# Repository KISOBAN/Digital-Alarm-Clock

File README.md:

This is a digital clock that has the option of being a stopwatch as well. This was done with the Raspberry PI Pico W using the C SDK and built using CMake.

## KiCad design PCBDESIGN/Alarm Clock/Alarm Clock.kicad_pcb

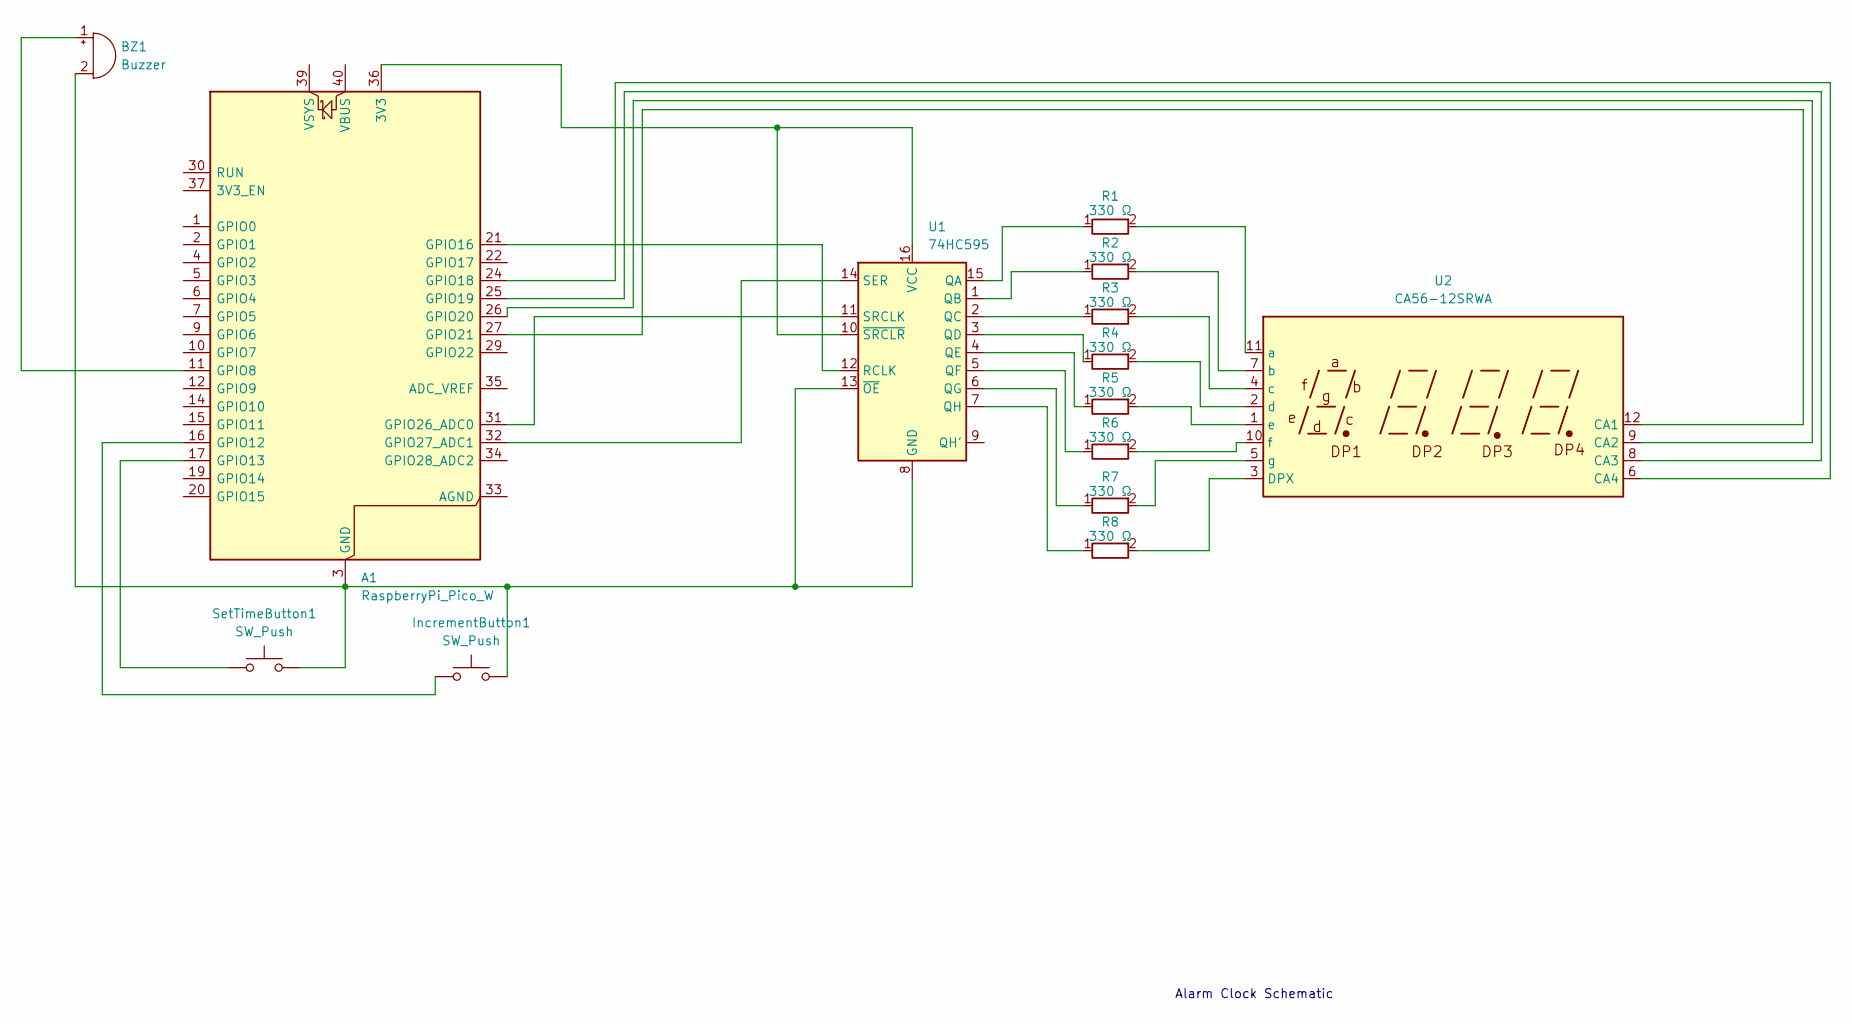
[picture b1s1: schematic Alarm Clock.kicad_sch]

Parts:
A1: RaspberryPi_Pico_W; RaspberryPi_Pico_W_SMD_HandSolder
BZ1: Buzzer; Buzzer_12x9.5RM7.6
IncrementButton1: SW_Push; SW_TH_Tactile_Omron_B3F-106x
R1, R2, R3, R4, R5, R6, R7, R8: 330 Ω; R_Axial_DIN0411_L9.9mm_D3.6mm_P12.70mm_Horizontal
SetTimeButton1: SW_Push; SW_TH_Tactile_Omron_B3F-106x
U1: 74HC595; SN74HCN595N
U2: CA56-12SRWA; 3461AS1 4 digit seven segment display

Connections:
unnamed: A1.36 (3V3), U1.10 (~SRCLR), U1.16 (VCC)
unnamed: A1.11 (GPIO8), BZ1.1 (+)
unnamed: A1.16 (GPIO12), IncrementButton1.1
unnamed: A1.17 (GPIO13), SetTimeButton1.1
unnamed: A1.21 (GPIO16), U1.12 (RCLK)
unnamed: A1.24 (GPIO18), U2.6 (CA4)
unnamed: A1.25 (GPIO19), U2.8 (CA3)
unnamed: A1.26 (GPIO20), U2.9 (CA2)
unnamed: A1.27 (GPIO21), U2.12 (CA1)
unnamed: A1.31 (GPIO26_ADC0), U1.11 (SRCLK)
unnamed: A1.32 (GPIO27_ADC1), U1.14 (SER)
unnamed: A1.3 (GND), A1.8 (GND), A1.13 (GND), A1.18 (GND), A1.23 (GND), A1.28 (GND), A1.38 (GND), BZ1.2 (-), IncrementButton1.2, SetTimeButton1.2, U1.8 (GND), U1.13 (~OE)
unnamed: R1.1, U1.15 (QA)
unnamed: R2.1, U1.1 (QB)
unnamed: R3.1, U1.2 (QC)
unnamed: R4.1, U1.3 (QD)
unnamed: R5.1, U1.4 (QE)
unnamed: R6.1, U1.5 (QF)
unnamed: R7.1, U1.6 (QG)
unnamed: R8.1, U1.7 (QH)
unnamed: R8.2, U2.3 (DPX)
unnamed: R1.2, U2.11 (a)
unnamed: R2.2, U2.7 (b)
unnamed: R3.2, U2.4 (c)
unnamed: R4.2, U2.2 (d)
unnamed: R5.2, U2.1 (e)
unnamed: R6.2, U2.10 (f)
unnamed: R7.2, U2.5 (g)

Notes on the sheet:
Alarm Clock Schematic

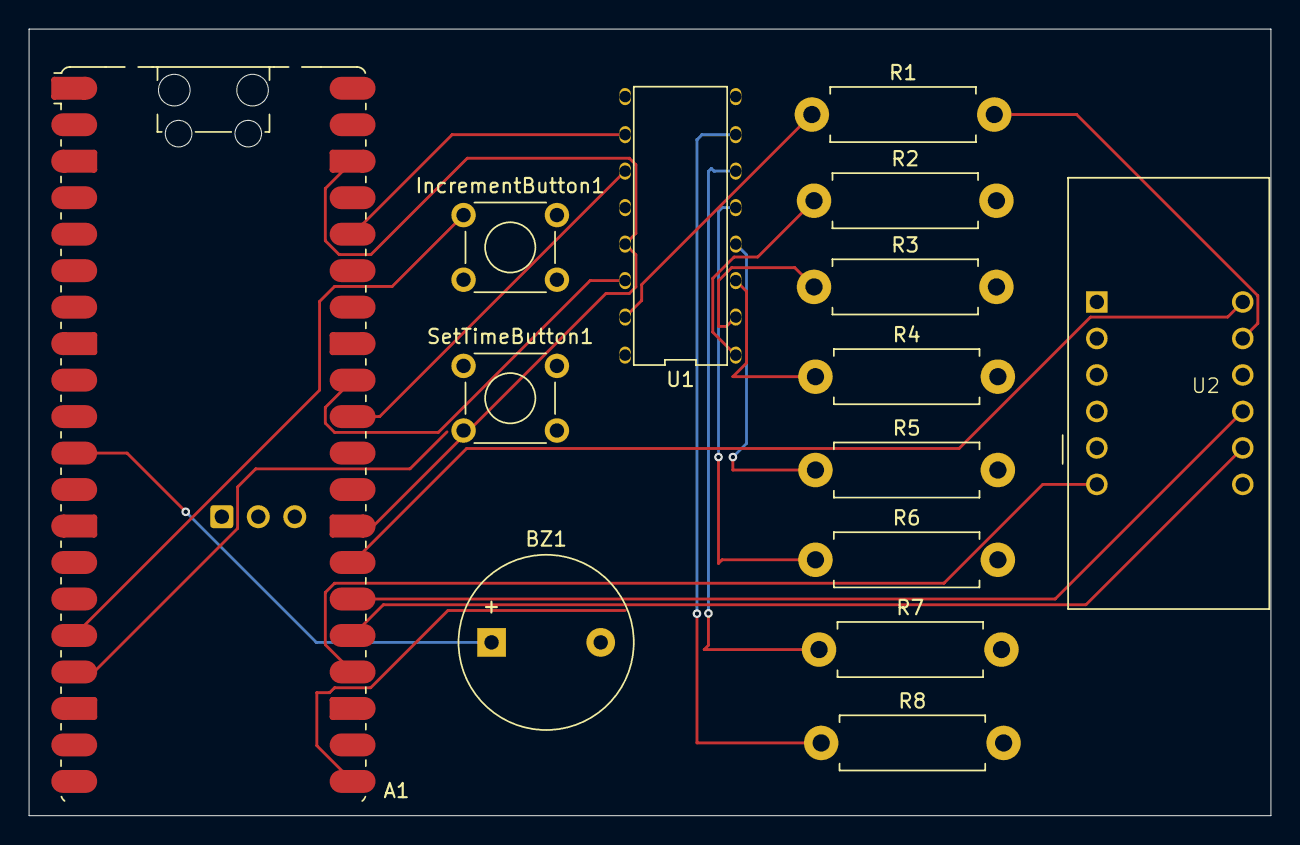
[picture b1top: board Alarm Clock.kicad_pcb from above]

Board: 2 copper layers, 86.5 x 54.8 mm, 14 parts (0 on the bottom side), 28 nets.

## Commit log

2026-02-09 Create s
2026-02-24 Rename Screenshot from 2026-02-24 15-10-03.png to board.png
2026-05-30 Create KicadFiles
